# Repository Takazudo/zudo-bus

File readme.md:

# Eurorack Bus Board (zudo-bus)

A bus board for distributing power from USB-PD power supply to Eurorack modular synthesizer modules.

## Documentation

**Main documentation is in the `/doc/` Docusaurus site**

```bash
cd doc
pnpm install
pnpm start
```

Open http://localhost:3333 in your browser to view the documentation.

## Project Overview

### Design Goals

Bus board for distributing power from zudo-pd USB-PD power supply to Eurorack modules.

- **Input**: Screw terminal connection (+12V, -12V, +5V, GND)
- **Output**: Multiple 16-pin IDC headers (Eurorack standard)
- **Capacity**: 8-12 module connections
- **Indicators**: LED status for each power rail

### Features

1. **Screw Terminal Input** - Easy connection from USB-PD power supply
2. **Multiple IDC Headers** - Standard Eurorack 16-pin connectors
3. **Per-Rail Protection** - Reverse polarity and overcurrent protection
4. **Visual Feedback** - LED indicators for power status
5. **JLCPCB Compatible** - All parts available from JLCPCB

## Repository Structure

- `/doc/` - Docusaurus documentation site **<- Main documentation**
- `/__inbox/` - Working directory (gitignored, temporary files)

## Related Projects

- [zudo-pd](https://github.com/Takazudo/zudo-pd) - USB-PD power supply that powers this bus board

## License

This project is open source. Hardware design files are free to use and modify.

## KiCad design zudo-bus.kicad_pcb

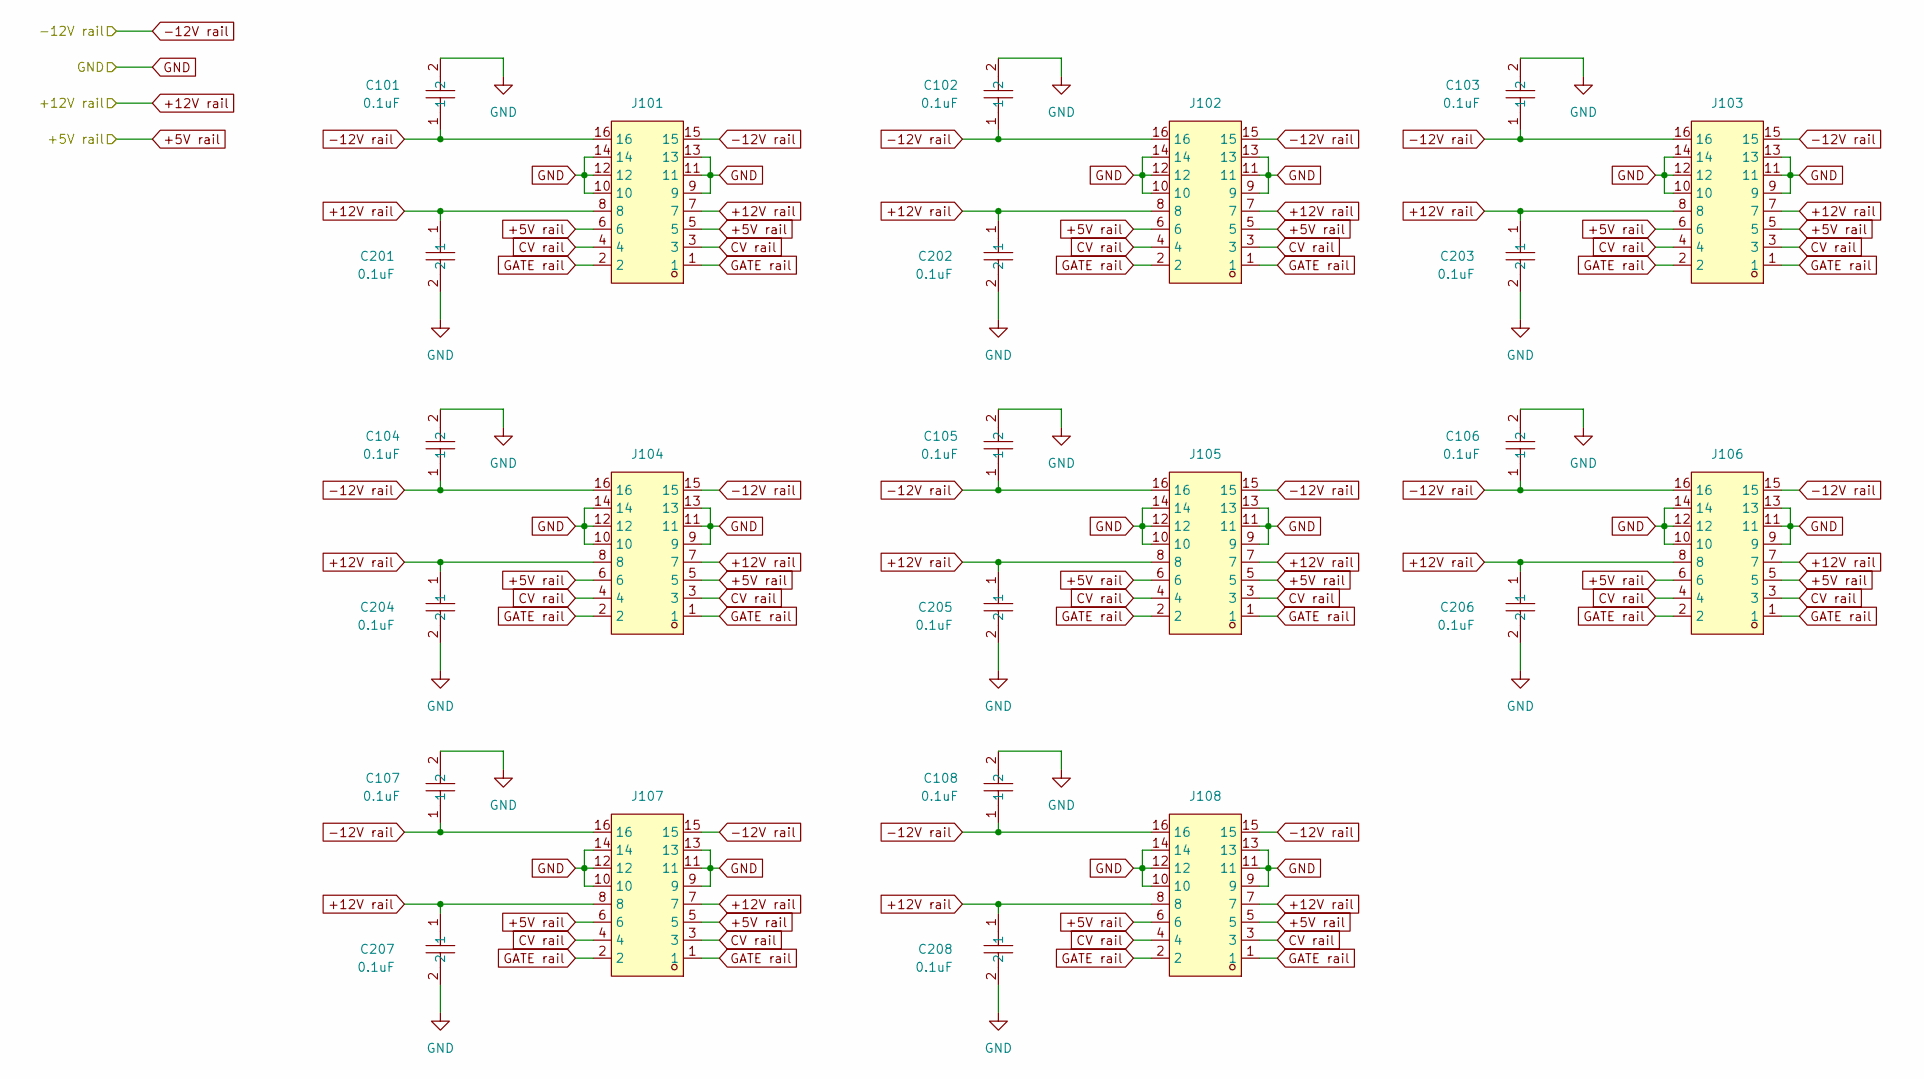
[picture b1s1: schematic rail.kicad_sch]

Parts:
C101, C102, C103, C104, C105, C106, C107, C108, C201, C202, C203, C204, C205, C206, C207, C208: 0.1uF; C0603; LCSC Part C14663
J101, J102, J103, J104, J105, J106, J107, J108: 2541WR-2X08P; HDR-TH_16P-P2.54-H-M-R2-C8-S2.54; LCSC Part C5383092

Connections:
+5V rail: J101.5, J101.6, J102.5, J102.6, J103.5, J103.6, J104.5, J104.6, J105.5, J105.6, J106.5, J106.6, J107.5, J107.6, J108.5, J108.6; also elsewhere on the board
+12V rail: C201.1, C202.1, C203.1, C204.1, C205.1, C206.1, C207.1, C208.1, J101.7, J101.8, J102.7, J102.8, J103.7, J103.8, J104.7, J104.8, J105.7, J105.8, J106.7, J106.8, J107.7, J107.8, J108.7, J108.8; also elsewhere on the board
-12V rail: C101.1, C102.1, C103.1, C104.1, C105.1, C106.1, C107.1, C108.1, J101.15, J101.16, J102.15, J102.16, J103.15, J103.16, J104.15, J104.16, J105.15, J105.16, J106.15, J106.16, J107.15, J107.16, J108.15, J108.16; also elsewhere on the board
CV rail: J101.3, J101.4, J102.3, J102.4, J103.3, J103.4, J104.3, J104.4, J105.3, J105.4, J106.3, J106.4, J107.3, J107.4, J108.3, J108.4
GATE rail: J101.1, J101.2, J102.1, J102.2, J103.1, J103.2, J104.1, J104.2, J105.1, J105.2, J106.1, J106.2, J107.1, J107.2, J108.1, J108.2
GND: C101.2, C102.2, C103.2, C104.2, C105.2, C106.2, C107.2, C108.2, C201.2, C202.2, C203.2, C204.2, C205.2, C206.2, C207.2, C208.2, J101.9, J101.10, J101.11, J101.12, J101.13, J101.14, J102.9, J102.10, J102.11, J102.12, J102.13, J102.14, J103.9, J103.10, J103.11, J103.12, J103.13, J103.14, J104.9, J104.10, J104.11, J104.12, J104.13, J104.14, J105.9, J105.10, J105.11, J105.12, J105.13, J105.14, J106.9, J106.10, J106.11, J106.12, J106.13, J106.14, J107.9, J107.10, J107.11, J107.12, J107.13, J107.14, J108.9, J108.10, J108.11, J108.12, J108.13, J108.14; also elsewhere on the board

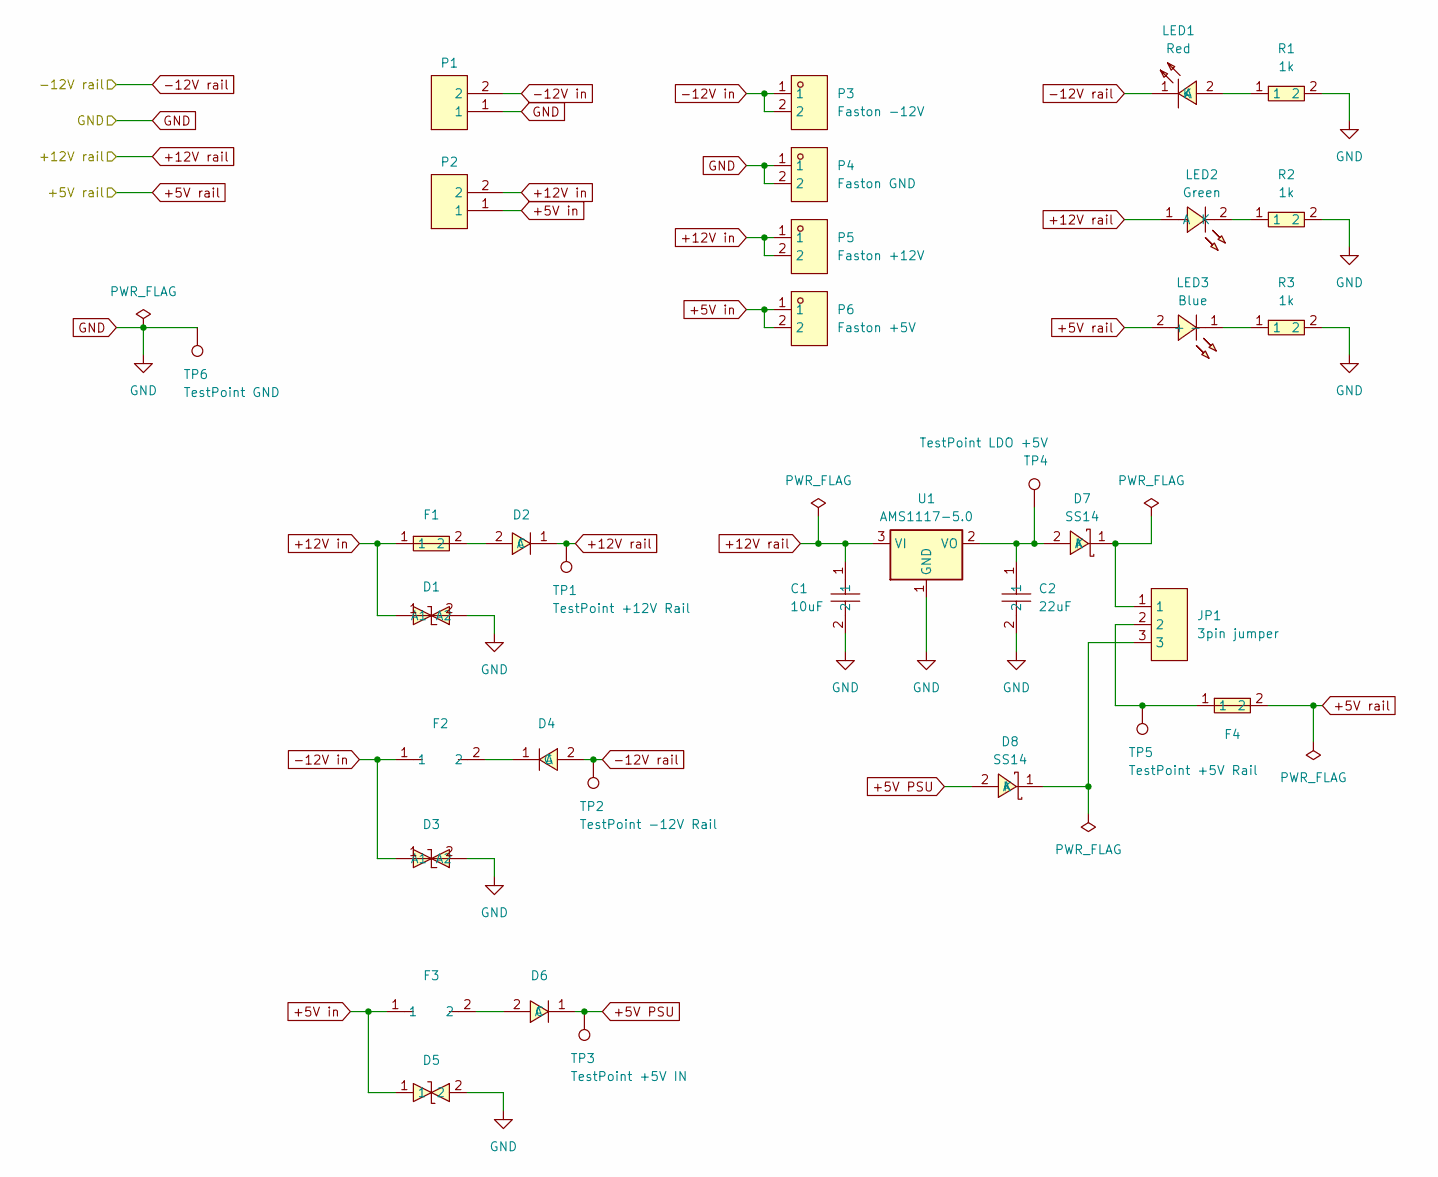
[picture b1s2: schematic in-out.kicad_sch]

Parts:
C1: 10uF; C0805; LCSC Part C15850
C2: 22uF; C0805; LCSC Part C45783
D1, D3: SMF12CA_C353317; SOD-123FL_L2.8-W1.8-LS3.7-BI; LCSC Part C353317
D2, D4, D6: SM4007PL; SOD-123F_L2.8-W1.8-LS3.7-RD; LCSC Part C64898
D5: SMF5.0CA_C908214; SOD-123FL_L2.8-W1.8-LS3.7-BI; LCSC Part C908214
D7, D8: SS14; SMA_L4.2-W2.6-LS5.0-RD_1; LCSC Part C2480
F1: BSMD1812-200-30V; F1812; LCSC Part C960026
F2, F3: BSMD1812-150-33V; F1812; LCSC Part C883154
F4: BSMD1812-110-33V; F1812; LCSC Part C883150
JP1: 3pin jumper; HDR-TH_3P-P2.54-V-M-1; LCSC Part C49257
LED1: Red; LED0603-RD; LCSC Part C2286
LED2: Green; LED0603-FD; LCSC Part C19171392
LED3: Blue; LED0603-RD; LCSC Part C5382145
P1, P2: WJ500V-5.08-2P-14-00A; CONN-TH_2P-P5.00_WJ500V-5.08-2P; LCSC Part C8465
P3: Faston -12V; CONN-TH_1217754-1; LCSC Part C305825
P4: Faston GND; CONN-TH_1217754-1; LCSC Part C305825
P5: Faston +12V; CONN-TH_1217754-1; LCSC Part C305825
P6: Faston +5V; CONN-TH_1217754-1; LCSC Part C305825
R1, R2, R3: 1k; R0805; LCSC Part C25623
TP1: TestPoint +12V Rail; TestPoint_Pad_D1.5mm
TP2: TestPoint -12V Rail; TestPoint_Pad_D1.5mm
TP3: TestPoint +5V IN; TestPoint_Pad_D1.5mm
TP4: TestPoint LDO +5V; TestPoint_Pad_D1.5mm
TP5: TestPoint +5V Rail; TestPoint_Pad_D1.5mm
TP6: TestPoint GND; TestPoint_Pad_D1.5mm
U1: AMS1117-5.0; SOT-223-3_TabPin2

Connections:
+5V PSU: D6.1 (C), D8.2 (A), TP3.1
+5V in: D5.1, F3.1, P2.1, P6.1, P6.2
+5V rail: F4.2, LED3.2 (+); also elsewhere on the board
+12V in: D1.1 (A2), F1.1, P2.2, P5.1, P5.2
+12V rail: C1.1, D2.1 (C), LED2.1 (A), TP1.1, U1.3 (VI); also elsewhere on the board
-12V in: D3.1 (A2), F2.1, P1.2, P3.1, P3.2
-12V rail: D4.2 (A), LED1.1 (K), TP2.1; also elsewhere on the board
GND: C1.2, C2.2, D1.2 (A1), D3.2 (A1), D5.2, P1.1, P4.1, P4.2, R1.2, R2.2, R3.2, TP6.1, U1.1 (GND); also elsewhere on the board
unnamed: D2.2 (A), F1.2
unnamed: D4.1 (C), F2.2
unnamed: D6.2 (A), F3.2
unnamed: C2.1, D7.2 (A), TP4.1, U1.2 (VO)
unnamed: D7.1 (K), JP1.1
unnamed: D8.1 (K), JP1.3
unnamed: F4.1, JP1.2, TP5.1
unnamed 17: LED1.2 (A), R1.1; also elsewhere on the board
unnamed 18: LED2.2 (K), R2.1; also elsewhere on the board
unnamed 19: LED3.1 (-), R3.1; also elsewhere on the board

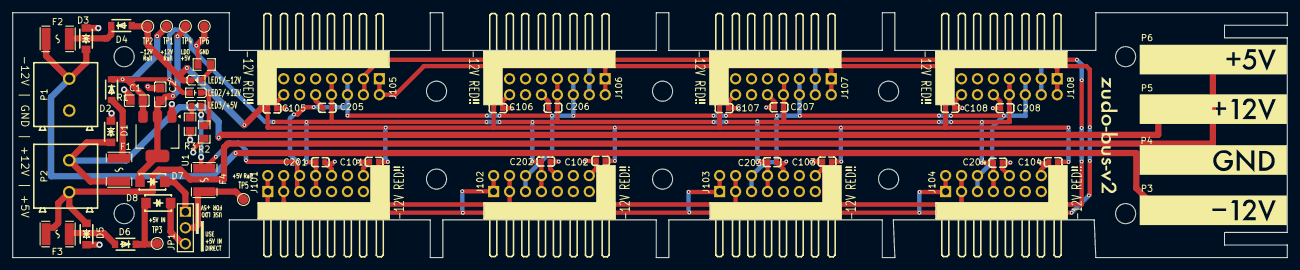
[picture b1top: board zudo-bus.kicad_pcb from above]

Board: 2 copper layers, 203.0 x 39.0 mm, 58 parts (0 on the bottom side), 20 nets.

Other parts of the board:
LED1/-12V: Red; LED0603-RD
LED2/+12V: Green; LED0603-FD
LED3/+5V: Blue; LED0603-RD

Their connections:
+5V rail: LED3/+5V.2 (+); also elsewhere on the board
+12V rail: LED2/+12V.1 (A); also elsewhere on the board
-12V rail: LED1/-12V.1 (K); also elsewhere on the board
unnamed 17: LED1/-12V.2 (A); also elsewhere on the board
unnamed 18: LED2/+12V.2 (K); also elsewhere on the board
unnamed 19: LED3/+5V.1 (-); also elsewhere on the board

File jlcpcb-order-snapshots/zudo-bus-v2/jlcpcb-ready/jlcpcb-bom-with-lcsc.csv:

Comment,Designator,Footprint,JLCPCB Part #
2541WR-2X08P,"J101,J102,J103,J104,J105,J106,J107,J108",eurorack-power-16pin,C5383092
Faston -12V,P3,power-faston-pin,C305825
Faston GND,P4,power-faston-pin,C305825
Faston +12V,P5,power-faston-pin,C305825
Faston +5V,P6,power-faston-pin,C305825
SS14,"D7,D8",SMA_L4.2-W2.6-LS5.0-RD_1,C2480
0.1uF,"C101,C102,C103,C104,C105,C106,C107,C108,C201,C202,C203,C204,C205,C206,C207,C208",C0603,C14663
Red,LED1/-12V,LED0603-RD,C2286
1k,"R1,R2,R3",R0805,C25623
SMF12CA_C353317,"D1,D3",SOD-123FL_L2.8-W1.8-LS3.7-BI,C353317
BSMD1812-150-33V,"F2,F3",F1812,C883154
WJ500V-5.08-2P-14-00A,"P1,P2",CONN-TH_2P-P5.00_WJ500V-5.08-2P,C8465
Green,LED2/+12V,LED0603-FD,C19171392
BSMD1812-200-30V,F1,F1812,C960026
SM4007PL,"D2,D4,D6",SOD-123F_L2.8-W1.8-LS3.7-RD,C64898
3pin jumper,JP1,HDR-TH_3P-P2.54-V-M-1,C49257
Blue,LED3/+5V,LED0603-RD,C5382145
SMF5.0CA_C908214,D5,SOD-123FL_L2.8-W1.8-LS3.7-BI,C908214
AMS1117-5.0,U1,SOT-223-3_TabPin2,C6187
22uF,C2,C0805,C45783
BSMD1812-110-33V,F4,F1812,C883150
10uF,C1,C0805,C15850

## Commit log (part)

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2026-01-13 initialized sch
2026-02-04 Update KiCad schematic and PCB layout
    - Adjust IDC header positions and rotations in rail schematic
    - Update PCB layout with component placements
    - Update project configuration
2026-02-05 Add custom footprints and update PCB layout
    - Add eurorack-power-16pin footprint with custom silkscreen
    - Add power-faston-pin footprint for FASTON connectors
    - Update PCB layout with component placements
    - Add design resource file (zudo-bus-svg.ai)
2026-02-05 Add JLCPCB order files for v2 production
    - Add gerbers, BOM with LCSC numbers, and CPL for JLCPCB assembly
    - Update KiCad project files
